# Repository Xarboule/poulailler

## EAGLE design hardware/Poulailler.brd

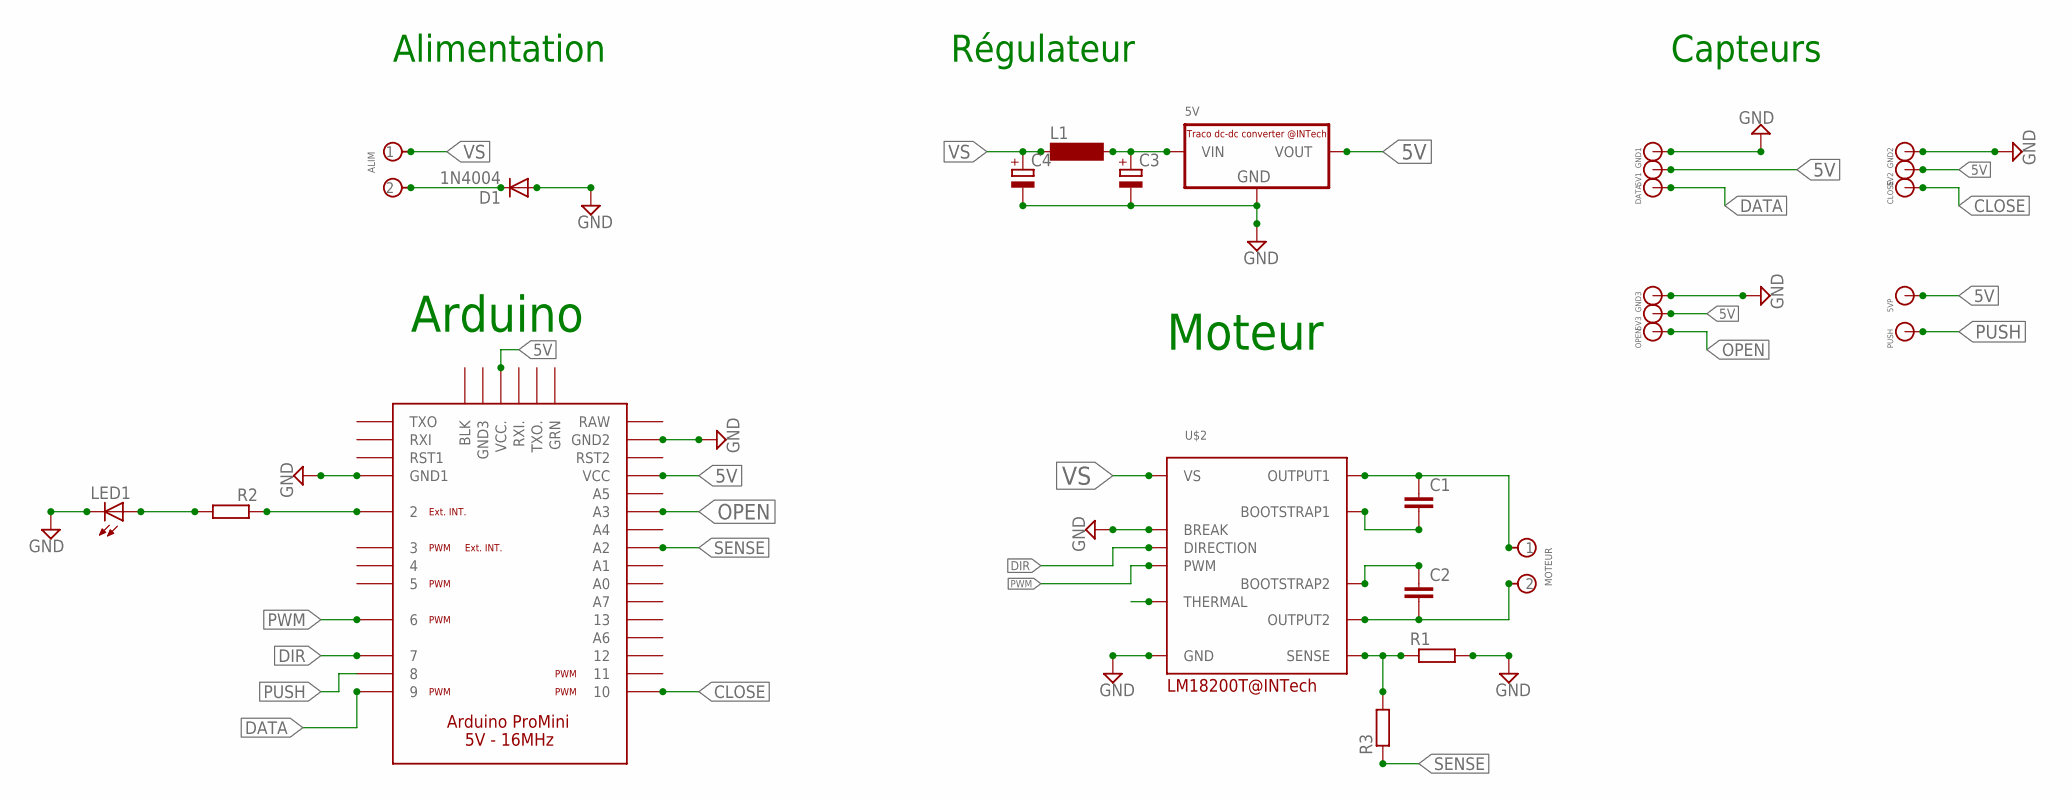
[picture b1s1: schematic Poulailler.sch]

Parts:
5V: R-78C-1.0_INTECH; SIP3_INTECH
5V1, 5V2, 5V3, 5VP: SOLPAD-1_CF_INTECH; SOLPAD-1
ALIM: BORNIER-2
C1, C2: C-EU025-025X050; C025-025X050
C3, C4: CPOL-EUE2,5-6E; E2,5-6E
CLOSE: SOLPAD-1_CF_INTECH; SOLPAD-1
D1: 1N4004; DO41-10
DATA: SOLPAD-1_CF_INTECH; SOLPAD-1
GND1, GND2, GND3: SOLPAD-1_CF_INTECH; SOLPAD-1
L1: SD12-1000; SD12_1000
LED1: LED3MM
MOTEUR: BORNIER-2
OPEN: SOLPAD-1_CF_INTECH; SOLPAD-1
PUSH: SOLPAD-1_CF_INTECH; SOLPAD-1
R1, R2, R3: R-EU_0204/5; 0204/5
U$1: ARDUINO_PRO_MINI
U$2: LM18200T_CF_INTECH

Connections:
5V: 5V.VOUT, 5V1.DATA, 5V2.DATA, 5V3.DATA, 5VP.DATA, U$1.VCC1 (VCC), U$1.VCC2 (VCC.)
CLOSE: CLOSE.DATA, U$1.10
DATA: DATA.DATA, U$1.9
DIR: U$1.7, U$2.3 (DIRECTION)
GND: 5V.GND, C3.-, C4.-, D1.A, GND1.DATA, GND2.DATA, GND3.DATA, LED1.K (C), R1.2, U$1.GND1, U$1.GND2, U$2.4 (BREAK), U$2.7 (GND)
unnamed: ALIM.2, D1.C
unnamed: R2.1, U$1.2
unnamed: 5V.VIN, C3.+, L1.2
unnamed: C1.1, MOTEUR.1, U$2.2 (OUTPUT1)
unnamed: C1.2, U$2.1 (BOOTSTRAP1)
unnamed: C2.1, U$2.11 (BOOTSTRAP2)
unnamed: C2.2, MOTEUR.2, U$2.10 (OUTPUT2)
unnamed: LED1.A, R2.2
OPEN: OPEN.DATA, U$1.A3
PUSH: PUSH.DATA, U$1.8
PWM: U$1.6, U$2.5 (PWM)
SENS: R1.1, R3.2, U$2.8 (SENSE)
SENSE: R3.1, U$1.A2
VS: ALIM.1, C4.+, L1.1, U$2.6 (VS)

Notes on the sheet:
Arduino
Moteur
Alimentation
Régulateur
Capteurs

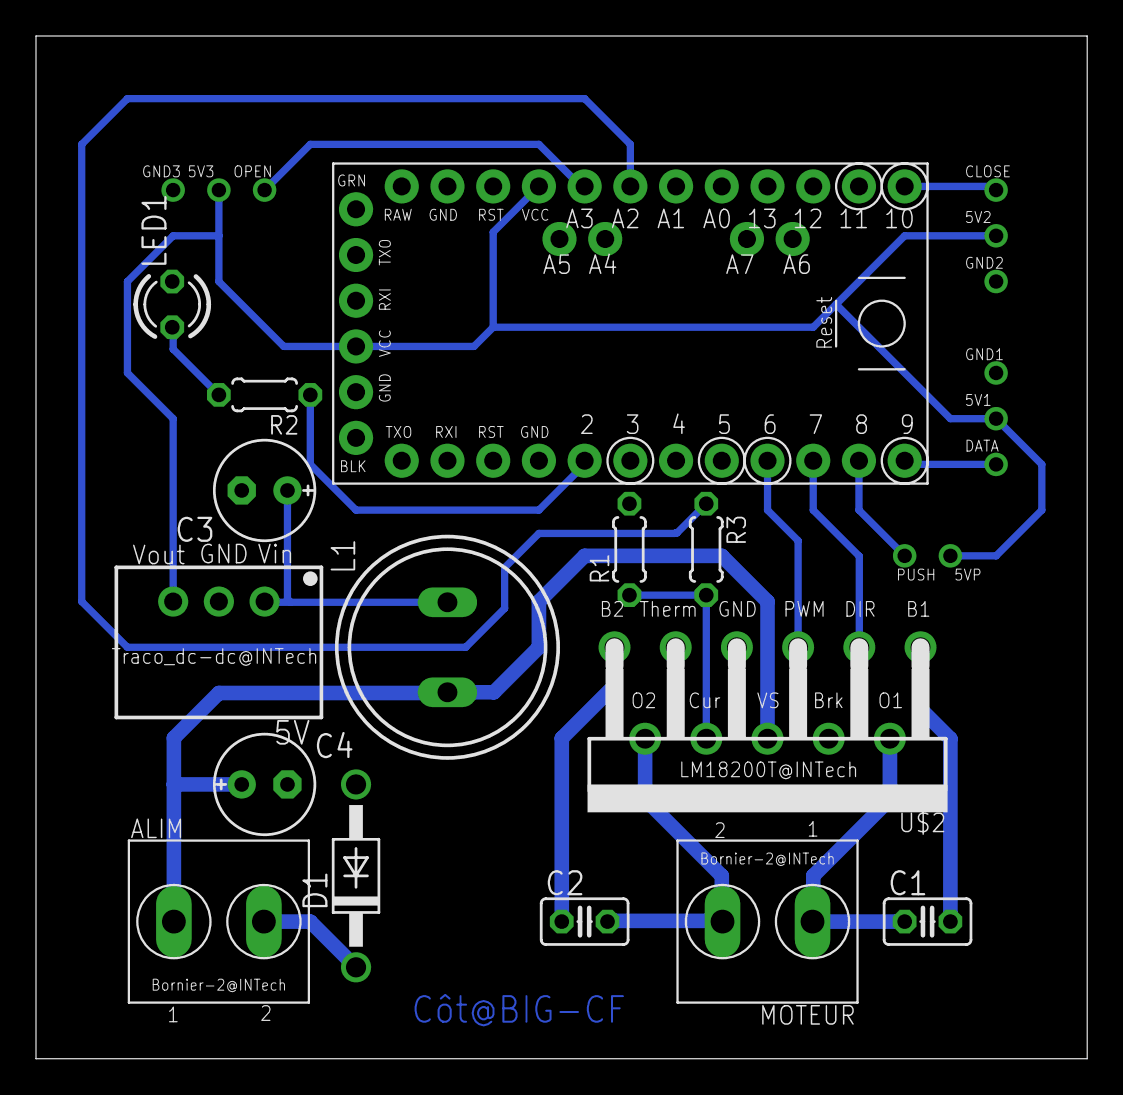
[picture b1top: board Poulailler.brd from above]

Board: 2 copper layers, 58.4 x 56.8 mm, 26 parts (0 on the bottom side), 19 nets.

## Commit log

2016-10-31 ajout de la partie électronique
2016-10-31 réattribution de pins

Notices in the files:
parts and their libraries:
Arduino_Pro_Mini: 2015 © S&G Cie.
